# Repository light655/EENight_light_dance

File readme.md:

# 把電還給機之夜
Don't try this at home.

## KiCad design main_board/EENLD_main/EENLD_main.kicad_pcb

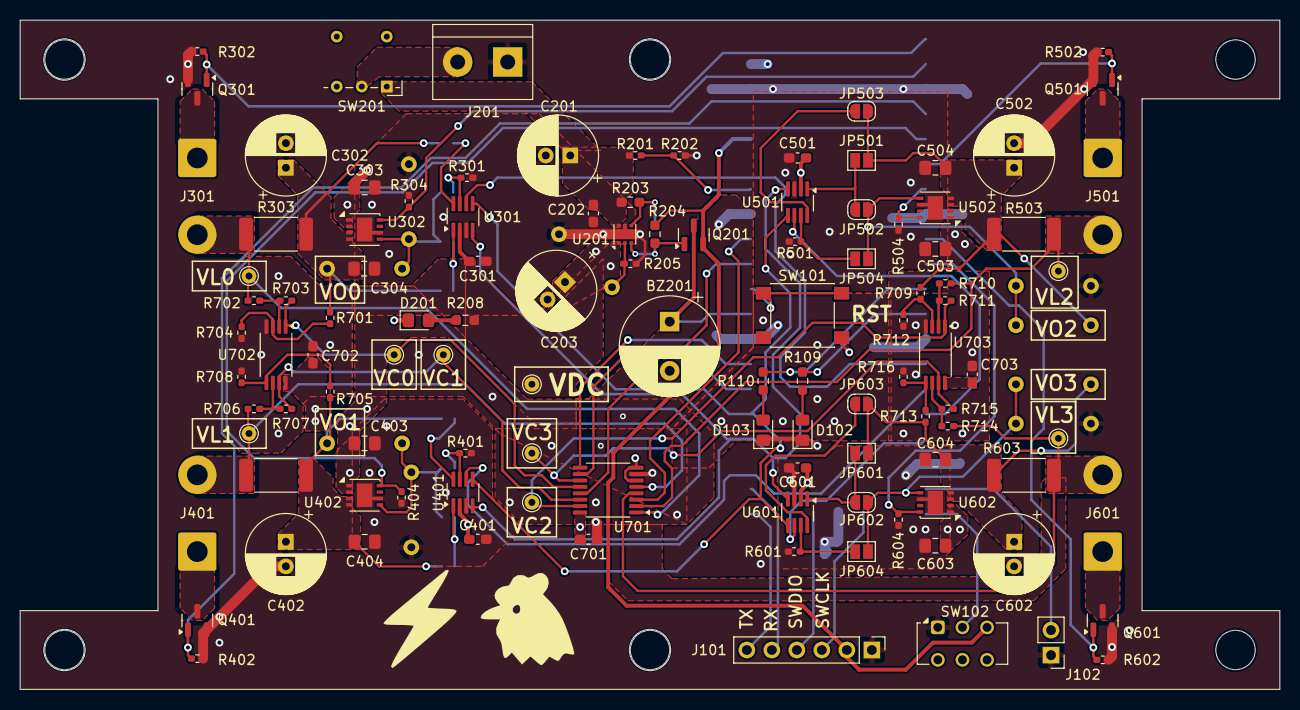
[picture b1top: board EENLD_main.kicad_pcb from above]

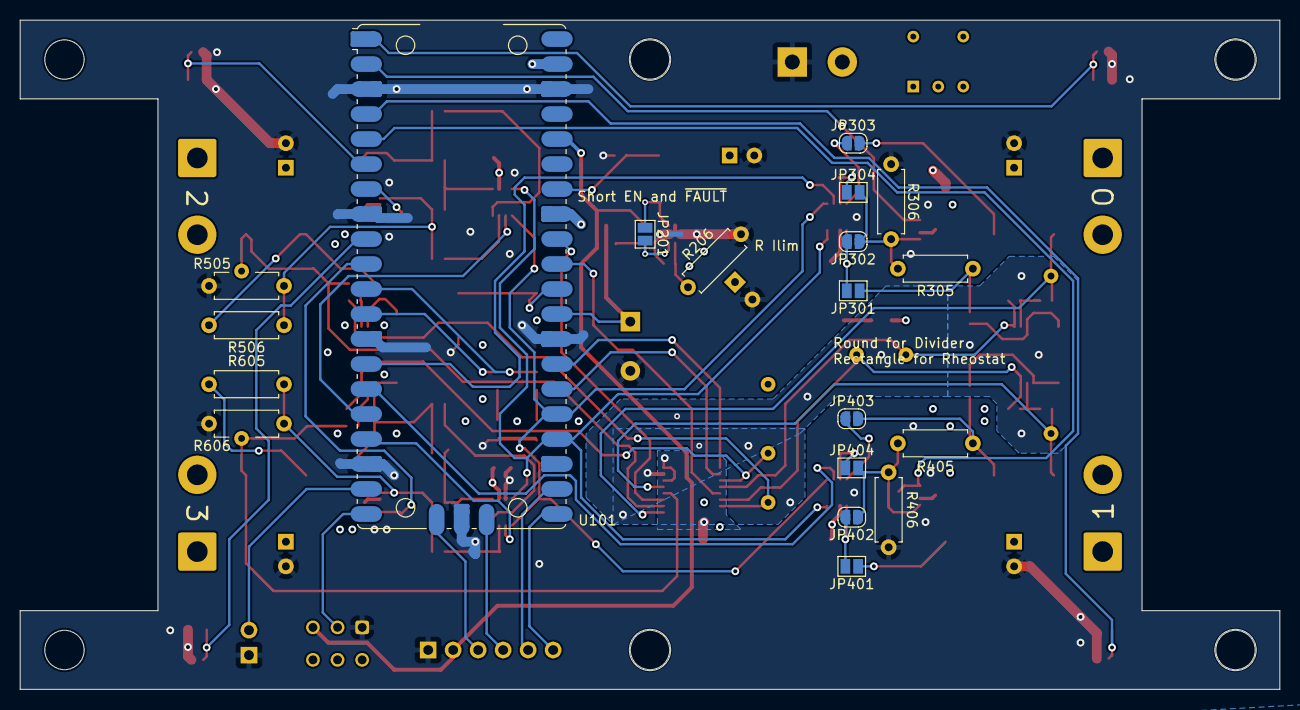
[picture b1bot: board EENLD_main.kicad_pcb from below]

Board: 4 copper layers, 128.0 x 68.0 mm, 129 parts (19 on the bottom side), 81 nets.

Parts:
BZ201: Buzzer; CP_Radial_D10.0mm_P5.00mm
C201, C203, C302, C402, C502, C602: 100u; CP_Radial_D8.0mm_P2.50mm
C202, C301, C401, C501, C601, C701, C702, C703: 100n; C_0603_1608Metric_Pad1.08x0.95mm_HandSolder
C303, C304, C403, C404, C503, C504, C603, C604: 2.2u; C_0805_2012Metric_Pad1.18x1.45mm_HandSolder
D102: green; LED_0805_2012Metric_Pad1.15x1.40mm_HandSolder
D103: red; LED_0805_2012Metric_Pad1.15x1.40mm_HandSolder
D201: Yellow; LED_0805_2012Metric_Pad1.15x1.40mm_HandSolder
J101: Conn_01x06_Pin; PinHeader_1x06_P2.54mm_Vertical
J102: Conn_01x02_Pin; PinHeader_1x02_P2.54mm_Vertical
J201: Conn_01x02_Socket; TerminalBlock_bornier-2_P5.08mm
J301, J401, J501, J601: Conn_01x02_Socket; SolderWire-1.5sqmm_1x02_P7.8mm_D1.7mm_OD3.9mm
JP201: SolderJumper_2_Open; SolderJumper-2_P1.3mm_Open_Pad1.0x1.5mm
JP301, JP304, JP401, JP404, JP501, JP504, JP601, JP604: Rectangle Jumper Open; SolderJumper-2_P1.3mm_Open_Pad1.0x1.5mm
JP302, JP303, JP402, JP403, JP502, JP503, JP602, JP603: Round Jumper Open; SolderJumper-2_P1.3mm_Open_RoundedPad1.0x1.5mm
Q201: AO3401A; SOT-23
Q301, Q401, Q501, Q601: AO3400A; SOT-23
R109, R110, R208: 1k; R_0603_1608Metric_Pad0.98x0.95mm_HandSolder
R201, R202, R205: 47k; R_0402_1005Metric_Pad0.72x0.64mm_HandSolder
R203, R204: 300k; R_0603_1608Metric_Pad0.98x0.95mm_HandSolder
R206: 47k; R_Axial_DIN0207_L6.3mm_D2.5mm_P7.62mm_Horizontal
R301, R401, R501, R601: 12k; R_0402_1005Metric_Pad0.72x0.64mm_HandSolder
R302, R304, R402, R404, R502, R504, R602, R604, R701, R702, R705, R706, R709, R710, R713, R714: 10k; R_0402_1005Metric_Pad0.72x0.64mm_HandSolder
R303, R403, R503, R603: 200m; R_2512_6332Metric_Pad1.40x3.35mm_HandSolder
R305, R306, R405, R406, R505, R506, R605, R606: 27k; R_Axial_DIN0207_L6.3mm_D2.5mm_P7.62mm_Horizontal
R703, R704, R707, R708, R711, R712, R715, R716: 200k; R_0402_1005Metric_Pad0.72x0.64mm_HandSolder
SW101: SW_Push; SW_Push_1P1T_NO_6x6mm_H9.5mm
SW102: SW_SPDT; SW_CK_JS202011CQN_DPDT_Straight
SW201: SW_SPDT; SW_Lever_1P2T_NKK_GW12LxH
TP201, TP302, TP402, TP502, TP602, TP701, TP702, TP703, TP704: TestPoint; TestPoint_THTPad_D1.5mm_Drill0.7mm
U101: Pico; RaspberryPi_Pico_Original_SMD
U201: TPS25200DRVR; WSON-6-1EP_2x2mm_P0.65mm_EP1x1.6mm_ThermalVias
U301, U401, U501, U601: AD5160BRJZ5; SOT-23-8_Handsoldering
U302, U402, U502, U602: RT9187QV; DFN-8-1EP_3x3mm_P0.65mm_EP1.55x2.4mm
U701: 74HC4052; TSSOP-16_4.4x5mm_P0.65mm
U702, U703: TLV9002; TSSOP-8_4.4x3mm_P0.65mm

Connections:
+3V3: J101.2, Q201.2 (S), R204.1, SW102.3 (C), U101.36 (3V3)
+BATT: C201.1, C202.1, R201.1, R203.1, SW201.1 (A), U201.6 (IN)
/ANALOG_A: U101.31 (GPIO26_ADC0), U701.13 (AN)
/ANALOG_B: U101.32 (GPIO27_ADC1), U701.3 (BN)
/Analogue signal processing/VC0: R703.1, TP701.1, U701.12 (A0), U702.1
/Analogue signal processing/VC1: R707.1, TP702.1, U701.14 (A1), U702.7
/Analogue signal processing/VC2: R711.1, TP703.1, U701.15 (A2), U703.1
/Analogue signal processing/VC3: R715.1, TP704.1, U701.11 (A3), U703.7
/Battery & protection/eFUSE_EN: JP201.1 (A), R203.2, U201.4 (EN)
/Battery & protection/eFUSE_~FAULT: JP201.2 (B), Q201.1 (G), R204.2, U201.3 (*FAULT)
/EL driver 0/LDO_feedback: JP302.1 (A), JP304.2 (B), R305.2, R306.1, U302.5 (ADJ)
/EL driver 1/LDO_feedback: JP402.1 (A), JP404.2 (B), R405.2, R406.1, U402.5 (ADJ)
/EL driver 2/LDO_feedback: JP502.1 (A), JP504.2 (B), R505.2, R506.1, U502.5 (ADJ)
/EL driver 3/LDO_feedback: JP602.1 (A), JP604.2 (B), R605.2, R606.1, U602.5 (ADJ)
/LDO_EN0: R304.1, U101.2 (GPIO1), U302.8 (EN)
/LDO_EN1: R404.1, U101.5 (GPIO3), U402.8 (EN)
/LDO_EN2: R504.1, U101.7 (GPIO5), U502.8 (EN)
/LDO_EN3: R604.1, U101.10 (GPIO7), U602.8 (EN)
/MUX_S0: U101.26 (GPIO20), U701.10 (S0)
/MUX_S1: U101.27 (GPIO21), U701.9 (S1)
/PWM0: Q301.1 (G), R302.1, U101.1 (GPIO0)
/PWM1: Q401.1 (G), R402.1, U101.4 (GPIO2)
/PWM2: Q501.1 (G), R502.1, U101.6 (GPIO4)
/PWM3: Q601.1 (G), R602.1, U101.9 (GPIO6)
/SPI_CLK: U101.24 (GPIO18), U301.4 (CLK), U401.4 (CLK), U501.4 (CLK), U601.4 (CLK)
/SPI_TX: U101.25 (GPIO19), U301.5 (SDI), U401.5 (SDI), U501.5 (SDI), U601.5 (SDI)
/SPI_~CS0: U101.14 (GPIO10), U301.6 (~CS)
/SPI_~CS1: U101.15 (GPIO11), U401.6 (~CS)
/SPI_~CS2: U101.16 (GPIO12), U501.6 (~CS)
/SPI_~CS3: U101.17 (GPIO13), U601.6 (~CS)
/SSD_CLK: R110.1, U101.11 (GPIO8)
/SSD_DATA: R109.1, U101.12 (GPIO9)
/SWCLK: J101.3, U101.41 (SWCLK)
/SWDIO: J101.4, U101.43 (SWDIO)
/T_SYNC: J102.2, U101.19 (GPIO14)
/UART0_RX: J101.5, U101.22 (GPIO17)
/UART0_TX: J101.6, U101.21 (GPIO16)
/VBAT_sense: R201.2, R202.1, U101.34 (GPIO28_ADC2)
/VL0: J301.2, R303.2, R702.1, TP302.1, U701.1 (B0)
/VL1: J401.2, R403.2, R706.1, TP402.1, U701.5 (B1)
/VL2: J501.2, R503.2, R710.1, TP502.1, U701.2 (B2)
/VL3: J601.2, R603.2, R714.1, TP602.1, U701.4 (B3)
/VO0: C302.1, C304.1, JP301.1 (A), JP303.2 (B), R303.1, R305.1, R701.1, U302.3 (VOUT), U302.4 (VOUT)
/VO1: C402.1, C404.1, JP401.1 (A), JP403.2 (B), R403.1, R405.1, R705.1, U402.3 (VOUT), U402.4 (VOUT)
/VO2: C502.1, C504.1, JP501.1 (A), JP503.2 (B), R503.1, R505.1, R709.1, U502.3 (VOUT), U502.4 (VOUT)
/VO3: C602.1, C604.1, JP601.1 (A), JP603.2 (B), R603.1, R605.1, R713.1, U602.3 (VOUT), U602.4 (VOUT)
/eFUSE_FAULT: BZ201.1 (+), Q201.3 (D), U101.29 (GPIO22)
GND: BZ201.2 (-), C201.2, C202.2, C203.2, C301.2, C302.2, C303.2, C304.2, C401.2, C402.2, C403.2, C404.2, C501.2, C502.2, C503.2, C504.2, C601.2, C602.2, C603.2, C604.2, C701.2, D102.1 (K), D103.1 (K), D201.1 (K), J101.1, J102.1, J201.1, Q301.2 (S), Q401.2 (S), Q501.2 (S), Q601.2 (S), R202.2, R205.2, R206.2, R301.2, R302.2, R304.2, R306.2, R401.2, R402.2, R404.2, R406.2, R501.2, R502.2, R504.2, R506.2, R601.2, R602.2, R604.2, R606.2, SW101.2, SW102.1 (A), U101.3 (GND), U101.8 (GND), U101.13 (GND), U101.18 (GND), U101.23 (GND), U101.28 (GND), U101.38 (GND), U101.42 (GND), U201.5 (GND), U201.7 (EPAD), U301.3 (GND), U302.6 (GND), U302.9 (GND), U401.3 (GND), U402.6 (GND), U402.9 (GND), U501.3 (GND), U502.6 (GND), U502.9 (GND), U601.3 (GND), U602.6 (GND), U602.9 (GND), U701.6 (~E), U701.8 (GND)
GNDA: C702.2, C703.2, R704.2, R708.2, R712.2, R716.2, U101.33 (AGND), U701.7 (VEE), U702.4 (V-), U703.4 (V-)
unnamed: D102.2 (A), R109.2
unnamed: D103.2 (A), R110.2
unnamed: D201.2 (A), R208.2
unnamed: J201.2, SW201.2 (B)
unnamed: J301.1, Q301.3 (D)
unnamed: J401.1, Q401.3 (D)
unnamed: J501.1, Q501.3 (D)
unnamed: J601.1, Q601.3 (D)
unnamed: JP301.2 (B), JP302.2 (B), U301.1 (W)
unnamed: JP303.1 (A), U301.8 (A)
unnamed: JP304.1 (A), R301.1, U301.7 (B)
unnamed: JP401.2 (B), JP402.2 (B), U401.1 (W)
unnamed: JP403.1 (A), U401.8 (A)
unnamed: JP404.1 (A), R401.1, U401.7 (B)
unnamed: JP501.2 (B), JP502.2 (B), U501.1 (W)
unnamed: JP503.1 (A), U501.8 (A)
unnamed: JP504.1 (A), R501.1, U501.7 (B)
unnamed: JP601.2 (B), JP602.2 (B), U601.1 (W)
unnamed: JP603.1 (A), U601.8 (A)
unnamed: JP604.1 (A), R601.1, U601.7 (B)
unnamed: SW102.2 (B), U101.20 (GPIO15)
unnamed: SW101.1, U101.30 (RUN)
unnamed: R205.1, R206.1, U201.2 (ILIM)
unnamed: R701.2, R704.1, U702.3 (+)
unnamed: R702.2, R703.2, U702.2 (-)
unnamed: R705.2, R708.1, U702.5 (+)
unnamed: R706.2, R707.2, U702.6 (-)
unnamed: R709.2, R712.1, U703.3 (+)
unnamed: R710.2, R711.2, U703.2 (-)
unnamed: R713.2, R716.1, U703.5 (+)
unnamed: R714.2, R715.2, U703.6 (-)
VDC: C203.1, C301.1, C303.1, C401.1, C403.1, C501.1, C503.1, C601.1, C603.1, C701.1, C702.1, C703.1, R208.1, TP201.1, U101.39 (VSYS), U201.1 (OUT), U301.2 (VDD), U302.1 (VIN), U302.2 (VIN), U401.2 (VDD), U402.1 (VIN), U402.2 (VIN), U501.2 (VDD), U502.1 (VIN), U502.2 (VIN), U601.2 (VDD), U602.1 (VIN), U602.2 (VIN), U701.16 (VDD), U702.8 (V+), U703.8 (V+)

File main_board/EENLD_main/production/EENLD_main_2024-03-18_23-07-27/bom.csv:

Designator,Footprint,Quantity,Value,LCSC Part #
BZ201,Buzzer_TDK_PS1240P02BT_D12.2mm_H6.5mm,1,Buzzer,
"C101, C202, C301, C401, C501, C601, C701, C702, C703",0603,9,100n,C14663
C102,CP_Radial_D8.0mm_P2.50mm,1,10u,
"C201, C203, C302, C402, C502, C602",CP_Radial_D8.0mm_P2.50mm,6,100u,
"C303, C304, C403, C404, C503, C504, C603, C604",0805,8,2.2u,C377773
D101,D1X8K,1,D198K,
D201,0805,1,Yellow,C2296
J101,PinHeader_1x06_P2.54mm_Vertical,1,Conn_01x06_Pin,
J102,PinHeader_1x02_P2.54mm_Vertical,1,Conn_01x02_Pin,
"J201, J301, J401, J501, J601",SolderWire-1.5sqmm_1x02_P7.8mm_D1.7mm_OD3.9mm,5,Conn_01x02_Socket,
"JP201, JP305, JP306, JP405, JP406, JP505, JP506, JP605, JP606",SolderJumper-2_P1.3mm_Open_Pad1.0x1.5mm,9,SolderJumper_2_Open,
"JP301, JP304, JP401, JP404, JP501, JP504, JP601, JP604",SolderJumper-2_P1.3mm_Open_Pad1.0x1.5mm,8,Rectangle Jumper Open,
"JP302, JP303, JP402, JP403, JP502, JP503, JP602, JP603",SolderJumper-2_P1.3mm_Open_RoundedPad1.0x1.5mm,8,Round Jumper Open,
Q201,SOT-23,1,AO3401A,C15127
"Q301, Q401, Q501, Q601",SOT-23,4,AO3400A,C20917
"R101, R102, R103, R104, R105, R106, R107, R108",0603,8,330,C23138
"R201, R202, R205",0402,3,47k,C25792
"R203, R204",0603,2,300k,C23024
"R207, R302, R304, R402, R404, R502, R504, R602, R604, R701, R702, R705, R706, R709, R710, R713, R714",0402,17,10k,C25744
R208,0603,1,1k,C21190
"R301, R401, R501, R601",0402,4,12k,C25752
"R303, R403, R503, R603",2512,4,200m,C309648
"R703, R704, R707, R708, R711, R712, R715, R716",0402,8,200k,C25764
SW101,SW_PUSH_6mm,1,SW_Push,
"SW102, SW103",SW_CK_JS202011CQN_DPDT_Straight,2,SW_SPDT,
SW201,SW_Lever_1P2T_NKK_GW12LxH,1,SW_SPDT,
"TP201, TP202, TP301, TP302, TP303, TP304, TP401, TP402, TP403, TP404, TP501, TP502, TP503, TP504, TP601, TP602, TP603, TP604, TP701, TP702, TP703, TP704",TestPoint_THTPad_D1.5mm_Drill0.7mm,22,TestPoint,
U102,SO-16_3.9x9.9mm_P1.27mm,1,74HC595,C5947
U201,WSON-6-1EP_2x2mm_P0.65mm_EP1x1.6mm_ThermalVias,1,TPS25200DRVR,C128401
"U301, U401, U501, U601",SOT-23-8_Handsoldering,4,AD5160BRJZ5,C578142
"U302, U402, U502, U602",DFN-8-1EP_3x3mm_P0.65mm_EP1.55x2.4mm,4,RT9187QV,C147970
U701,SO-16_3.9x9.9mm_P1.27mm,1,74HC4052,C11350
"U702, U703",SOIC-8_3.9x4.9mm_P1.27mm,2,TLV9002,C398360

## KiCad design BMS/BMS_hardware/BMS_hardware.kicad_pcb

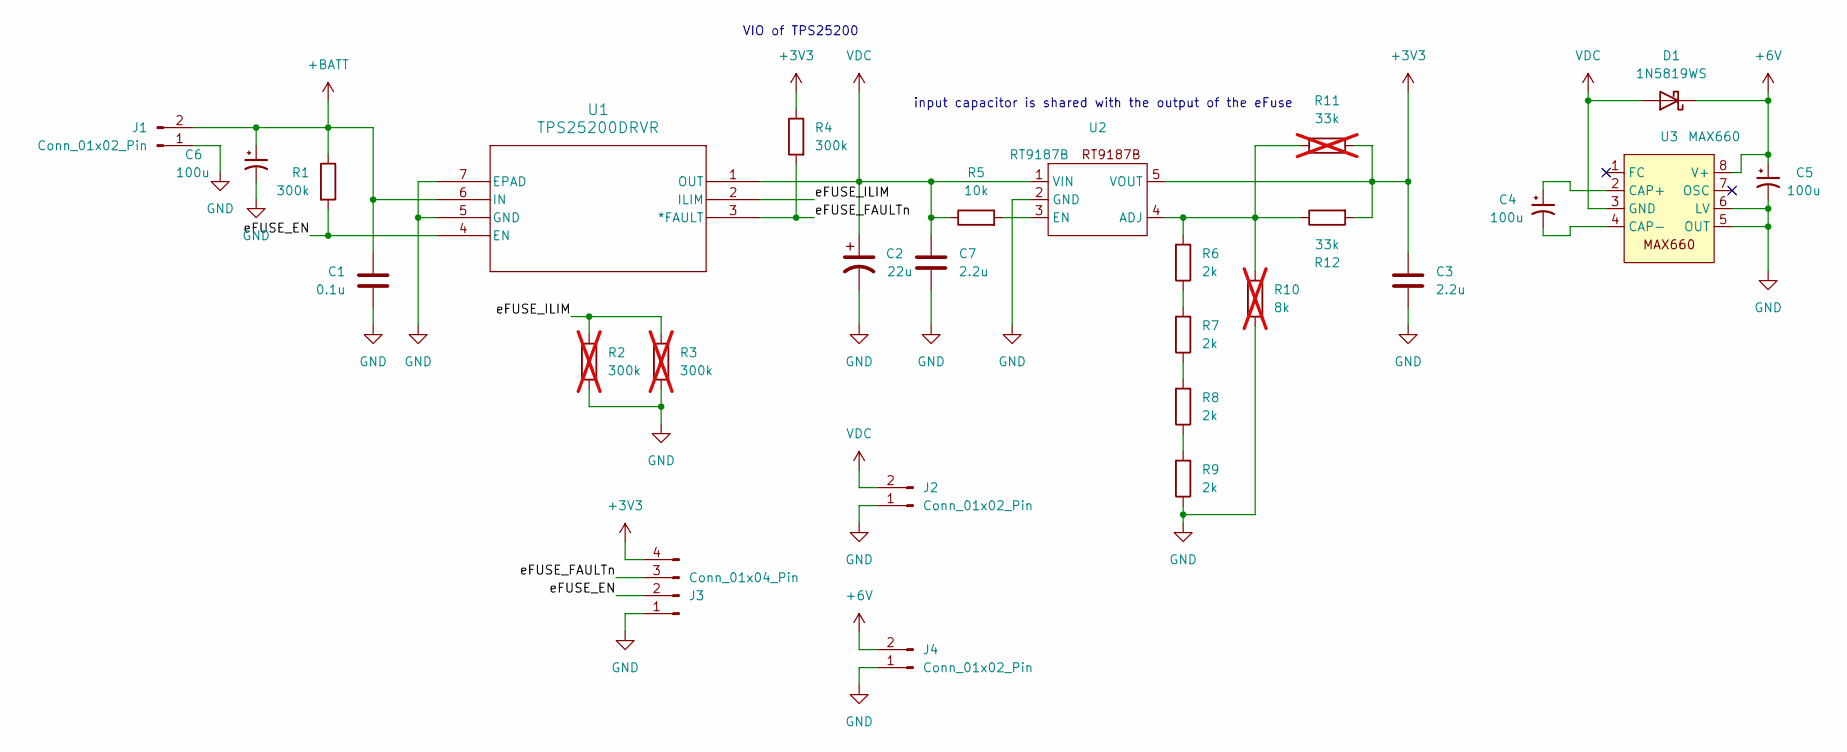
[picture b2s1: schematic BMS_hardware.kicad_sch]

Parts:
C1: 0.1u; C_0603_1608Metric_Pad1.08x0.95mm_HandSolder; LCSC C14663
C2: 22u; CP_Radial_D6.3mm_P2.50mm
C3, C7: 2.2u; C_0805_2012Metric_Pad1.18x1.45mm_HandSolder; LCSC C377773
C4, C5, C6: 100u; CP_Radial_D6.3mm_P2.50mm
D1: 1N5819WS; D_SOD-323; LCSC C191023
J1, J2, J4: Conn_01x02_Pin; TerminalBlock_Phoenix_MKDS-1,5-2-5.08_1x02_P5.08mm_Horizont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
J3: Conn_01x04_Pin; PinHeader_1x04_P2.54mm_Vertical
R1, R4: 300k; R_0603_1608Metric_Pad0.98x0.95mm_HandSolder; LCSC C23024
R2, R3: 300k; R_Axial_DIN0207_L6.3mm_D2.5mm_P7.62mm_Horizontal; not fitted
R5: 10k; R_0603_1608Metric_Pad0.98x0.95mm_HandSolder; LCSC C25804
R6, R7, R8, R9: 2k; R_0603_1608Metric_Pad0.98x0.95mm_HandSolder; LCSC C22975
R10: 8k; R_Axial_DIN0207_L6.3mm_D2.5mm_P7.62mm_Horizontal; not fitted
R11: 33k; R_Axial_DIN0207_L6.3mm_D2.5mm_P7.62mm_Horizontal; not fitted
R12: 33k; R_0603_1608Metric_Pad0.98x0.95mm_HandSolder; LCSC C4216
U1: TPS25200DRVR; WSON-6-1EP_2x2mm_P0.65mm_EP1x1.6mm_ThermalVias; LCSC C128401
U2: RT9187B; SOT-23-5_HandSoldering; LCSC C3031681
U3: MAX660; SOIC-8_3.9x4.9mm_P1.27mm

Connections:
+3V3: C3.1, J3.4, R4.1, R11.2, R12.2, U2.5 (VOUT)
+6V: C5.1, D1.1 (K), J4.2, U3.8 (V+)
+BATT: C1.1, C6.1, J1.2, R1.1, U1.6 (IN)
/eFUSE_EN: J3.2, R1.2, U1.4 (EN)
/eFUSE_FAULTn: J3.3, R4.2, U1.3 (*FAULT)
/eFUSE_ILIM: R2.1, R3.1, U1.2 (ILIM)
GND: C1.2, C2.2, C3.2, C5.2, C6.2, C7.2, J1.1, J2.1, J3.1, J4.1, R2.2, R3.2, R9.1, R10.2, U1.5 (GND), U1.7 (EPAD), U2.2 (GND), U3.5 (OUT), U3.6 (LV)
unnamed: R6.1, R7.2
unnamed: R7.1, R8.2
unnamed: R8.1, R9.2
unnamed: R6.2, R10.1, R11.1, R12.1, U2.4 (ADJ)
unnamed: R5.2, U2.3 (EN)
unnamed: C4.1, U3.2 (CAP+)
unnamed: C4.2, U3.4 (CAP-)
VDC: C2.1, C7.1, D1.2 (A), J2.2, R5.1, U1.1 (OUT), U2.1 (VIN), U3.3 (GND)

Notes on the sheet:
VIO of TPS25200
input capacitor is shared with the output of the eFuse

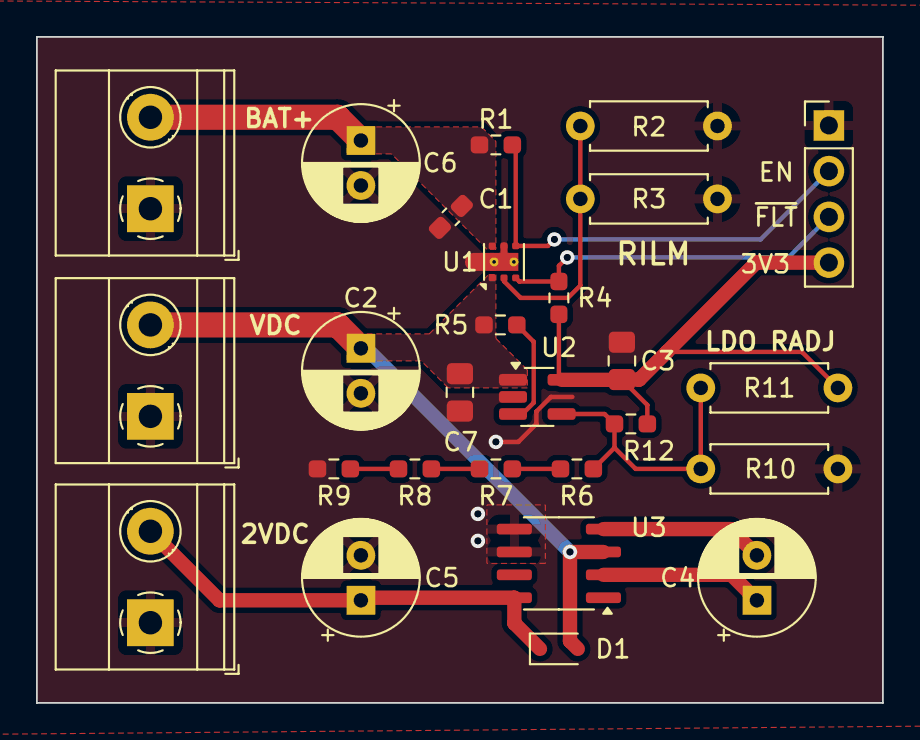
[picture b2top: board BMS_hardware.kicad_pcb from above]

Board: 2 copper layers, 47.0 x 37.0 mm, 27 parts (0 on the bottom side), 15 nets.

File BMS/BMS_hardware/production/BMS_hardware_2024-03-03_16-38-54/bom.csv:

Designator,Footprint,Quantity,Value,LCSC Part #
C1,0603,1,0.1u,C14663
"C3, C7",0805,2,2.2u,C377773
D1,D_SOD-323,1,1N5819WS,C191023
"R1, R4",0603,2,300k,C23024
R12,0603,1,33k,C4216
R5,0603,1,10k,C25804
"R6, R7, R8, R9",0603,4,2k,C22975
U1,WSON-6-1EP_2x2mm_P0.65mm_EP1x1.6mm_ThermalVias,1,TPS25200DRVR,C128401
U2,SOT-23-5_HandSoldering,1,RT9187B,C3031681

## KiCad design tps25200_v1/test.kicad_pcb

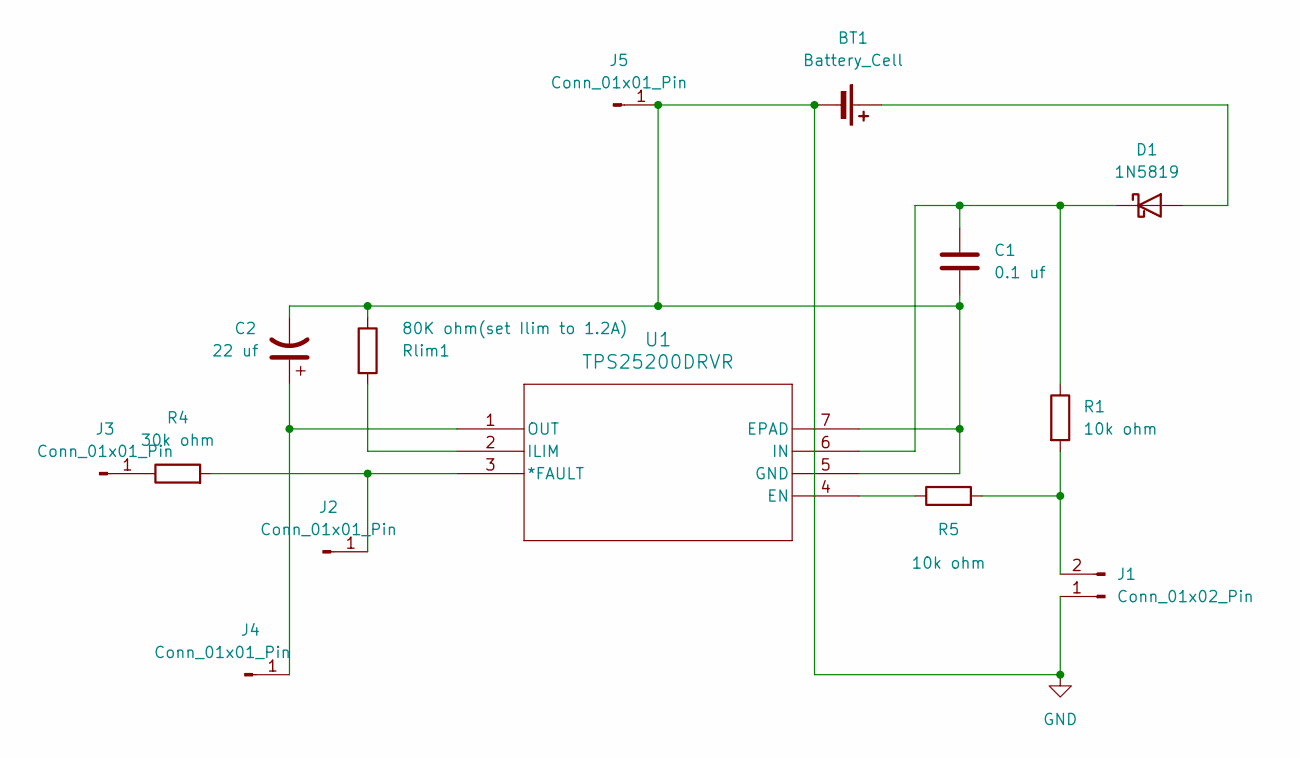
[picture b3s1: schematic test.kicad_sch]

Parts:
BT1: Battery_Cell; BatteryHolder_MPD_BH-18650-PC2
C1: 0.1 uf; C_0603_1608Metric_Pad1.08x0.95mm_HandSolder
C2: 22 uf; CP_Radial_D8.0mm_P2.50mm
D1: 1N5819; D_DO-41_SOD81_P10.16mm_Horizontal
J1: Conn_01x02_Pin; PinHeader_1x02_P2.54mm_Vertical
J2, J3, J4, J5: Conn_01x01_Pin; PinHeader_1x01_P2.54mm_Vertical
R1, R5: 10k ohm; R_0603_1608Metric_Pad0.98x0.95mm_HandSolder
R4: 30k ohm; R_0603_1608Metric_Pad0.98x0.95mm_HandSolder
Rlim1: 80K ohm(set Ilim to 1.2A); R_0603_1608Metric_Pad0.98x0.95mm_HandSolder
U1: TPS25200DRVR; DRV6_1X1P6_TEX

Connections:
GND: BT1.2 (-), C1.2, C2.2, J1.1, J5.1, Rlim1.1, U1.5 (GND), U1.7 (EPAD)
unnamed: BT1.1 (+), D1.2 (A)
unnamed: C1.1, D1.1 (K), R1.1, U1.6 (IN)
unnamed: J1.2, R1.2, R5.2
unnamed: J2.1, R4.2, U1.3 (*FAULT)
unnamed: J3.1, R4.1
unnamed: C2.1, J4.1, U1.1 (OUT)
unnamed: R5.1, U1.4 (EN)
unnamed: Rlim1.2, U1.2 (ILIM)

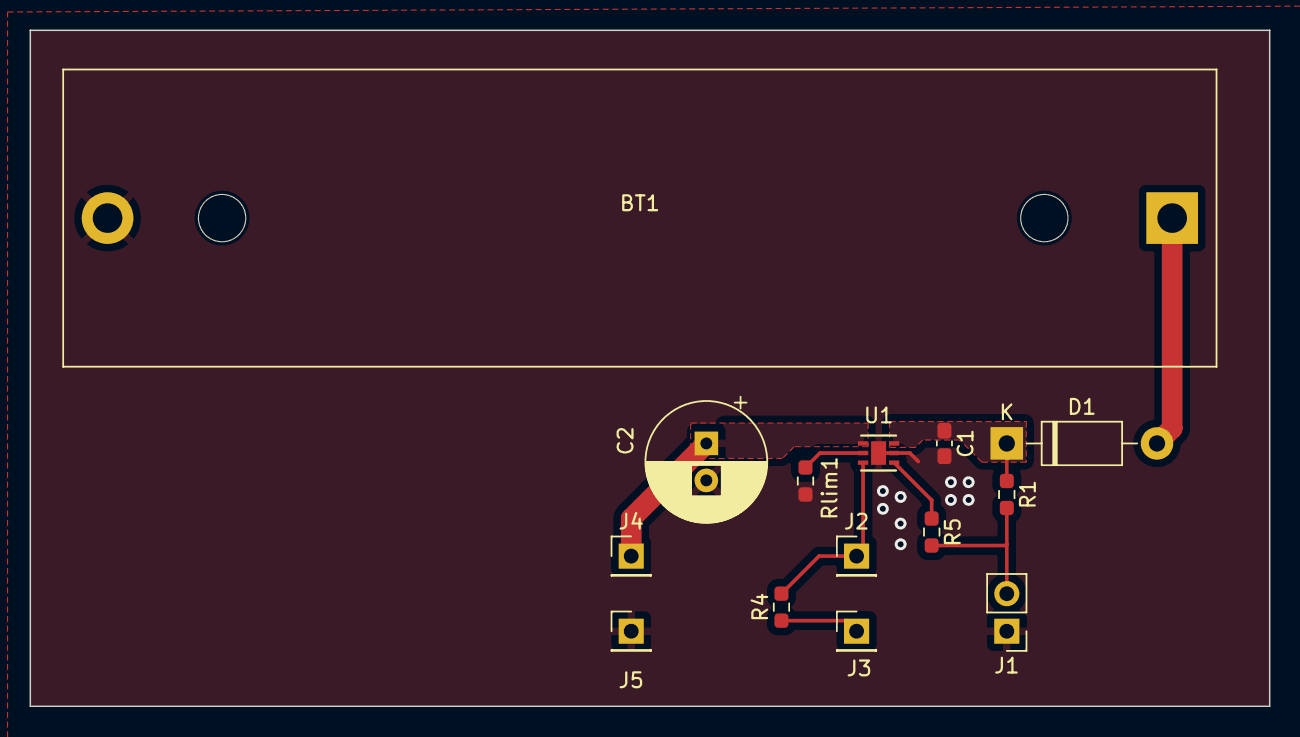
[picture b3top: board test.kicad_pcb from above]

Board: 2 copper layers, 83.8 x 45.7 mm, 14 parts (0 on the bottom side), 9 nets.

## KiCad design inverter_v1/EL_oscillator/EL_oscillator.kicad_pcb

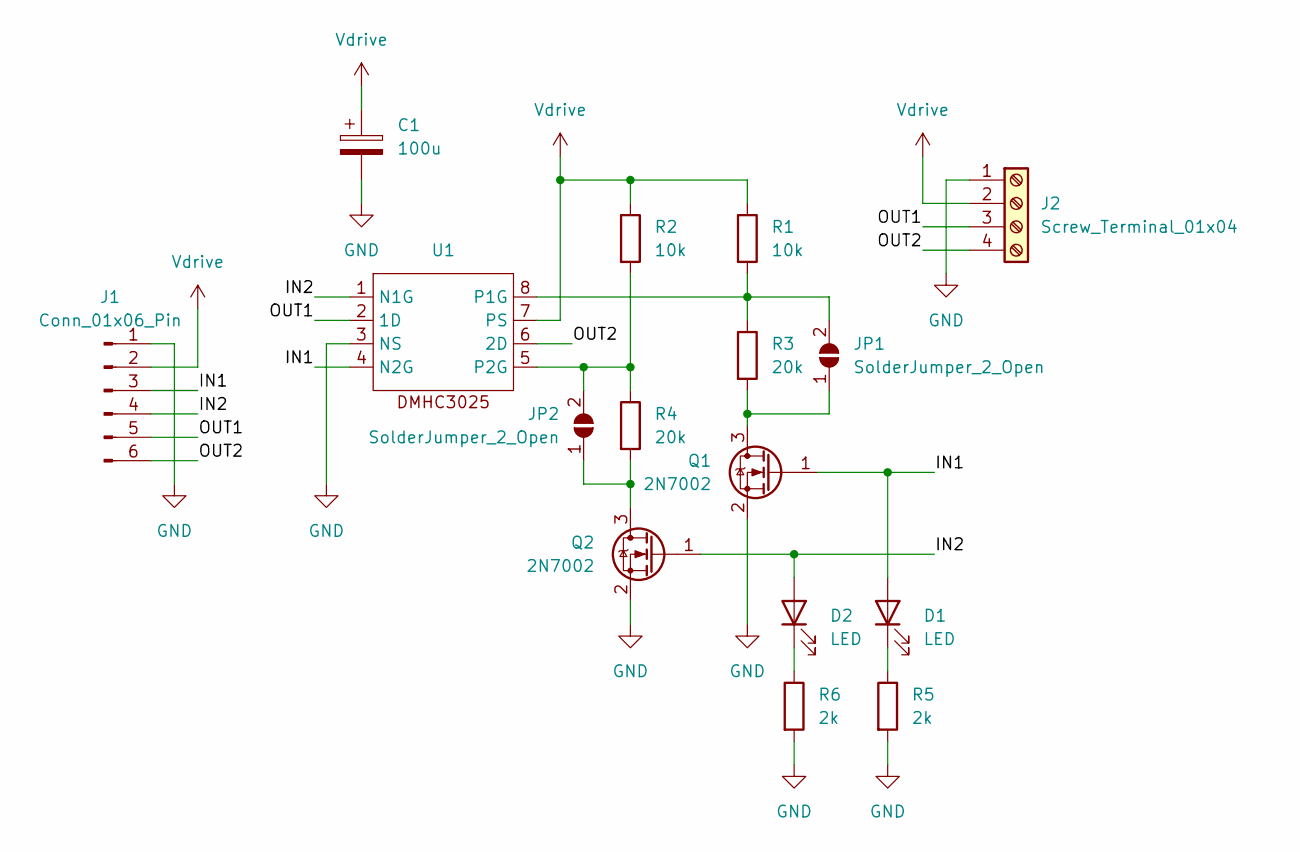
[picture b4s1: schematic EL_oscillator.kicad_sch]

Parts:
C1: 100u; CP_Radial_D5.0mm_P2.00mm
D1, D2: LED; LED_0603_1608Metric_Pad1.05x0.95mm_HandSolder; LCSC C2286
J1: Conn_01x06_Pin; PinHeader_1x06_P2.54mm_Vertical
J2: Screw_Terminal_01x04; TerminalBlock_bornier-4_P5.08mm
JP1, JP2: SolderJumper_2_Open; SolderJumper-2_P1.3mm_Open_RoundedPad1.0x1.5mm
Q1, Q2: 2N7002; SOT-23; LCSC C8545
R1, R2: 10k; R_0603_1608Metric_Pad0.98x0.95mm_HandSolder; LCSC C25804
R3, R4: 20k; R_0603_1608Metric_Pad0.98x0.95mm_HandSolder; LCSC C4184
R5, R6: 2k; R_0603_1608Metric_Pad0.98x0.95mm_HandSolder; LCSC C22975
U1: SO-8_3.9x4.9mm_P1.27mm; LCSC C156387

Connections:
/IN1: D1.2 (A), J1.3, Q1.1 (G), U1.4 (N2G)
/IN2: D2.2 (A), J1.4, Q2.1 (G), U1.1 (N1G)
/OUT1: J1.5, J2.3, U1.2 (1D)
/OUT2: J1.6, J2.4, U1.6 (2D)
GND: C1.2, J1.1, J2.1, Q1.2 (S), Q2.2 (S), R5.2, R6.2, U1.3 (NS)
unnamed: D1.1 (K), R5.1
unnamed: D2.1 (K), R6.1
unnamed: JP1.1 (A), Q1.3 (D), R3.2
unnamed: JP1.2 (B), R1.2, R3.1, U1.8 (P1G)
unnamed: JP2.1 (A), Q2.3 (D), R4.2
unnamed: JP2.2 (B), R2.2, R4.1, U1.5 (P2G)
Vdrive: C1.1, J1.2, J2.2, R1.1, R2.1, U1.7 (PS)

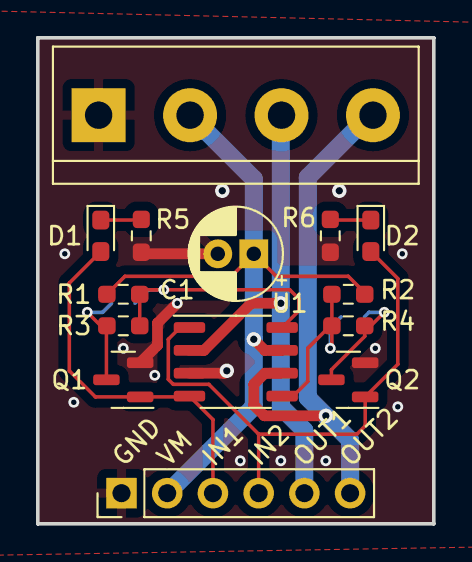
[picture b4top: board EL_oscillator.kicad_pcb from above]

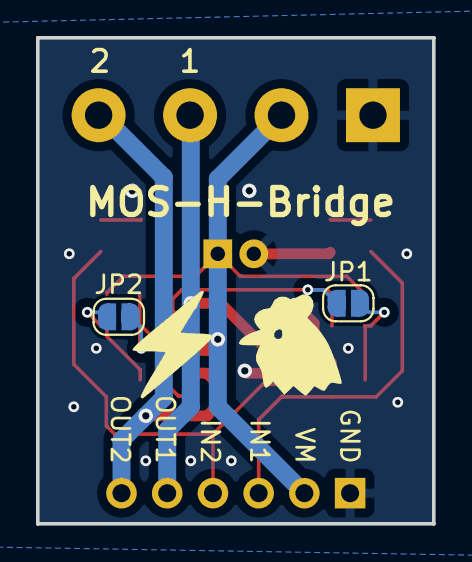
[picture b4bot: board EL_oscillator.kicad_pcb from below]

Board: 2 copper layers, 22.0 x 27.0 mm, 16 parts (2 on the bottom side), 12 nets.

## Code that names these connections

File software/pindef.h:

#ifndef PINDEF_H
#define PINDEF_H

#define LDO_EN0 1
#define LDO_EN1 3
#define LDO_EN2 5
#define LDO_EN3 7
#define PWM_PIN0 0
#define PWM_PIN1 2
#define PWM_PIN2 4
#define PWM_PIN3 6
#define SPI_CS0 10
#define SPI_CS1 11
#define SPI_CS2 12
#define SPI_CS3 13
#define SPI_CLK 18
#define SPI_TX 19
#define MUX_S0 20
#define MUX_S1 21
#define VC_SENSE 26
#define VL_SENSE 27
#define VBAT_SENSE 28
#define LED_R 8
#define LED_G 9
#define LED_PICO 25
#define T_SYNC 14

#endif

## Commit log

2024-02-23 First commit. Added readme.md
2024-02-23 Added H-bridge.
2024-02-23 Added basic tsp25200 circuit
2024-02-23 Added BT137 symbol.
2024-02-23 Added MOC3021M to schematic.
2024-03-01 New BMS schematic.
2024-03-02 Added MAX660 for voltage doubling.
2024-03-04 Added basic pwm dc step down funtion for pico
2024-03-17 First schematic version.
2024-03-20 Finished PCB layout v0.1.
2024-04-01 added midi2array
2024-04-04 Prettified midi2array.
2024-04-08 Added pictures for simulation.
2024-04-08 script to convert midiarray to video using ffmpeg
2024-04-12 Fixed command line argument in midi2array_mod
2024-04-16 fix the blinking frame , change to 60Hz , manual added
2024-04-18 update firmware
2024-04-21 updated midi2array to support fading
2024-04-23 dim / cre added
2024-04-24 fix light coding
2024-04-24 Fucked
2024-04-25 Fixed midi2array.
2024-04-26 Nothing to see here
2024-04-27 Fixed fading
2024-04-27 try to fix flase disable
2024-04-28 Changed LED pin.
2024-04-28 Fixed track issue.
2024-04-28 Tweaked Pico firmware
2024-04-28 fix sth fucked up
2024-04-28 Fxxx
